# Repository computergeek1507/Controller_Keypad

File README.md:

# Copyright and Disclaimer
Copyright: Scott Hanson

This documentation describes Open Hardware and is licensed under the CERN Open Hardware License Version 2 - Strongly Reciprocal. (CERN-OHL-S)

You may redistribute and modify this documentation under the terms of the CERN OHL-S-v2 (https://ohwr.org/cern_ohl_s_v2.txt). This documentation is distributed WITHOUT ANY EXPRESS OR IMPLIED WARRANTY, INCLUDING OF MERCHANTABILITY, SATISFACTORY QUALITY AND FITNESS FOR A PARTICULAR PURPOSE. Please see the CERN OHL v2-S for applicable conditions

**Under CERN OHL-S-v2, derivative work must be publicly released as defined in subsection 3.3**

# Controller Keypad

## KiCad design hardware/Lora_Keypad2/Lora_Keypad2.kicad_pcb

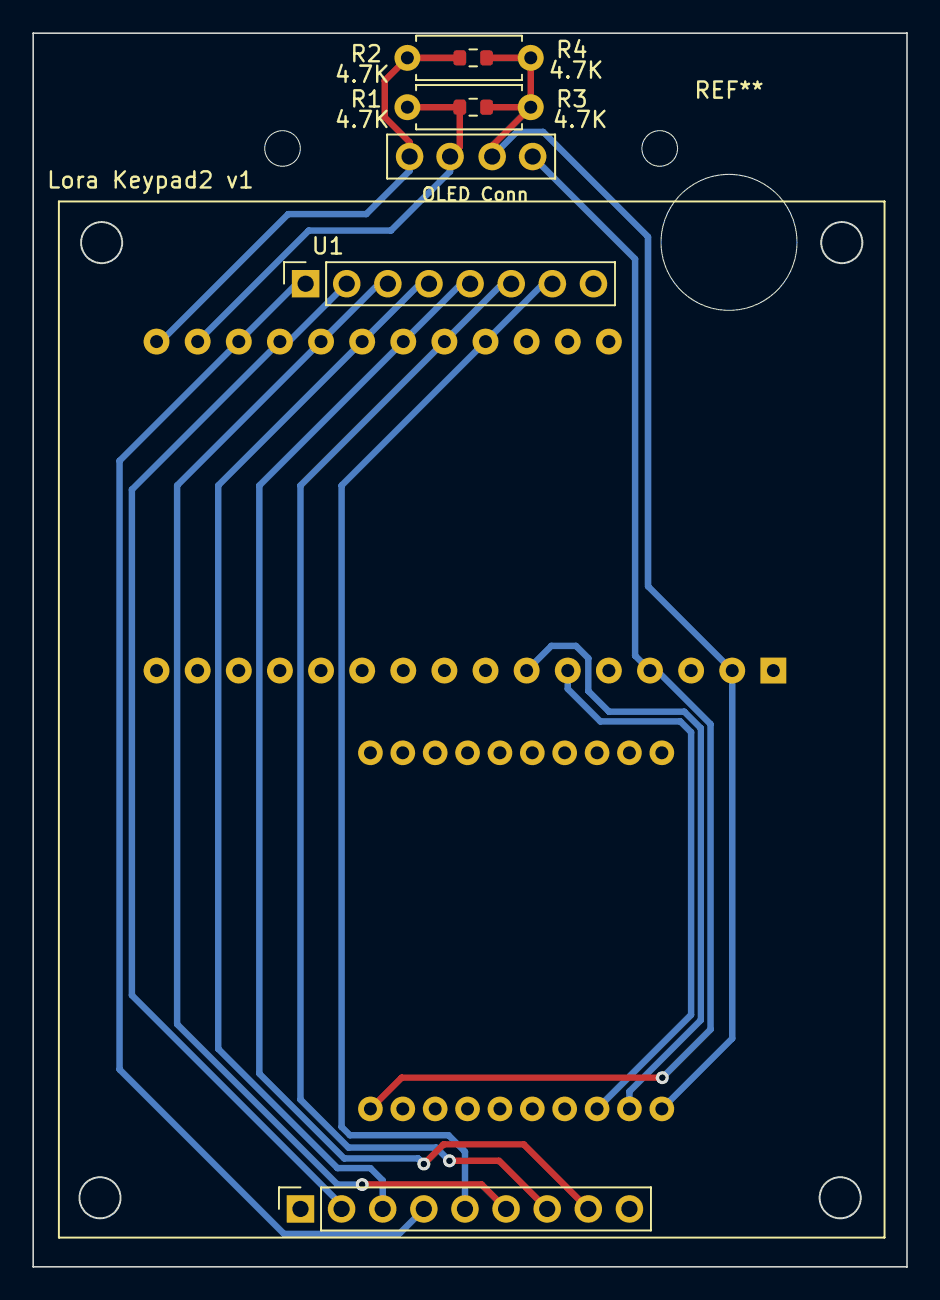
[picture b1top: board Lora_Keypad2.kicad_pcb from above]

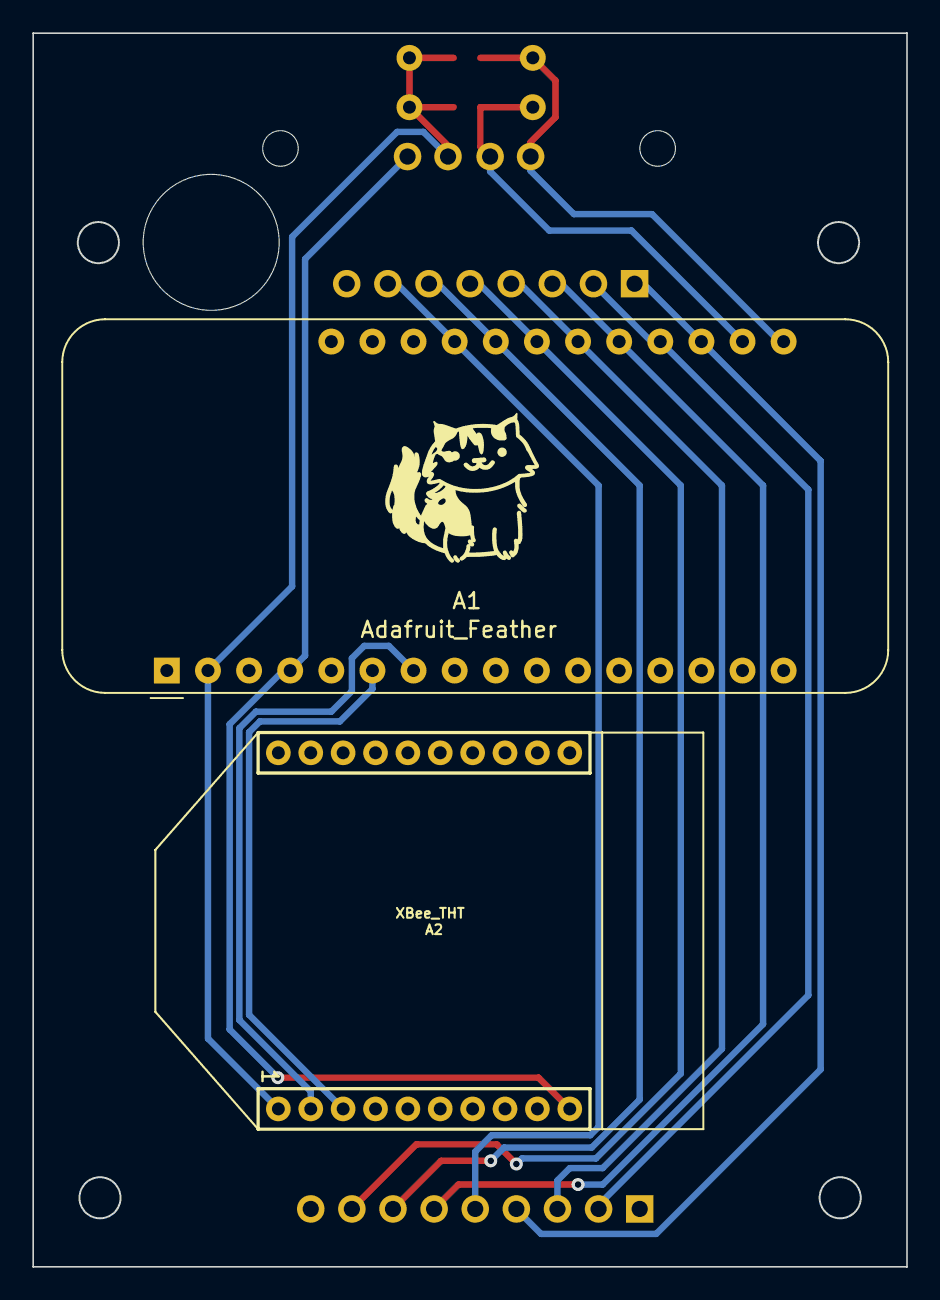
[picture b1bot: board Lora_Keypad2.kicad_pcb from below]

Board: 2 copper layers, 54.0 x 76.2 mm, 8 parts (2 on the bottom side), 13 nets.

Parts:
A1: Adafruit_Feather
A2: XBee_THT; XBEE
J1: OLED Conn; OLED-SSD1306-128X64-I2C-THT_2HOLE
R1, R2: 4.7K; R_0603_1608Metric
R3, R4: 4.7K; R_Axial_DIN0207_L6.3mm_D2.5mm_P7.62mm_Horizontal
U1: 3x4_keypad

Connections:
+3.3V: A1.2 (3V3), A2.1 (VCC), J1.3, R1.1, R2.1, R3.1, R4.1
C1: A1.19 (D0), U1.A1 (C1), U1.B4 (C1)
C2: A1.20 (D1), U1.A2 (C2), U1.B2 (C2)
C3: A1.21 (D2), U1.A3 (C3), U1.B6 (C3)
GND: A1.4 (GND), A2.10 (GND), J1.4
I2C_SCL: A1.18 (SCL), J1.2, R1.2, R3.2
I2C_SDA: A1.17 (SDA), J1.1, R2.2, R4.2
R1: A1.22 (D3), U1.A4 (R1), U1.B3 (R1)
R2: A1.23 (D4), U1.A5 (R2), U1.B8 (R2)
R3: A1.24 (D5), U1.A6 (R3), U1.B7 (R3)
R4: A1.25 (D6), U1.A7 (R4), U1.B5 (R4)
RX: A1.7 (A2), A2.2 (DOUT/DIO13)
TX: A1.6 (A1), A2.3 (DIN/~CONFIG/DIO14)

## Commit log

2023-09-14 added files
2023-09-14 Always show WebUI, added playlist commands
2023-11-03 working on case for hw2
